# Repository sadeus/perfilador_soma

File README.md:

# Perfilador/Polarimetro SOMA

## Contenido
Se crearon sensores optomecánicos portátiles, para poder medir cambios de los haces de los setups del laboratorio. Todo el marco del proyecto SOMA

### Indice de carpetas
- software: Software para la adquisición y visualización de las mediciones. Acá se efectúa el análisis de los datos obtenidos
- firmware: Código para el uC para el polarimetro/perfilador. Tiene un makefila con los métodos usuales
- circuito: Diseño del circuito impreso
- perfilador: Diseño mecánico del perfilador
- polarimetro: Diseño mecánico del polarimetro
- espectrometro: Diseño del circuito para el espectrómetro (EN PROGRESO)

## Instalación

Para poder instalar y usar el software/firmware de este proyecto es necesario tener [NodeJS](https://nodejs.org/es/):

- Linux, macOS: Instalación por manejador de paquetes, [aquí](https://nodejs.org/es/download/package-manager/)
- Windows: Descargar binario de la página oficial

En una command prompt o terminal escribir lo siguiente para instalar dependencias

```npm install```

Esto instala las dependencias de firmware y software. Para obtener ayuda de los comandos disponibles ejecutar

```npm run```

### Lista de comandos
- `npm run ip`: abre el puerto serie creado al conectar el uC y obtiene la ip del dispositivo
- `npm run start`: inicia el servidor web del software de adquisición. Por defecto se entra en un browser en http://localhost:9000
- `npm run compile`: compila el firmware. Para compilar el firmware, por ahora, es necesario logearse con `npm run login` y una cuenta de [particle.io](http://build.particle.io)
- `npm run upload`: Actualiza el firmware del uC por USB. Es necesario tener el uC en modo DFU (ver [acá](https://docs.particle.io/guide/getting-started/modes/photon/#dfu-mode-device-firmware-upgrade-))

## Dependencias

### Software
- Python v3.5.0
- Numpy v1.11.3
- Pandas v0.19.2
- Matplotlib v2.0.0
- Scipy v0.18.1
- Flask v0.12
- Web browser (Firefox, Chrome, Safari, _no funciona en IE_)

### Firmware
Para compilar, flashear y escuchar el puerto Serie del uC es necesario tener:
- NodeJS v6.0
- Particle-cli v1.21.0
- readline-sync (para interfaz interactiva)

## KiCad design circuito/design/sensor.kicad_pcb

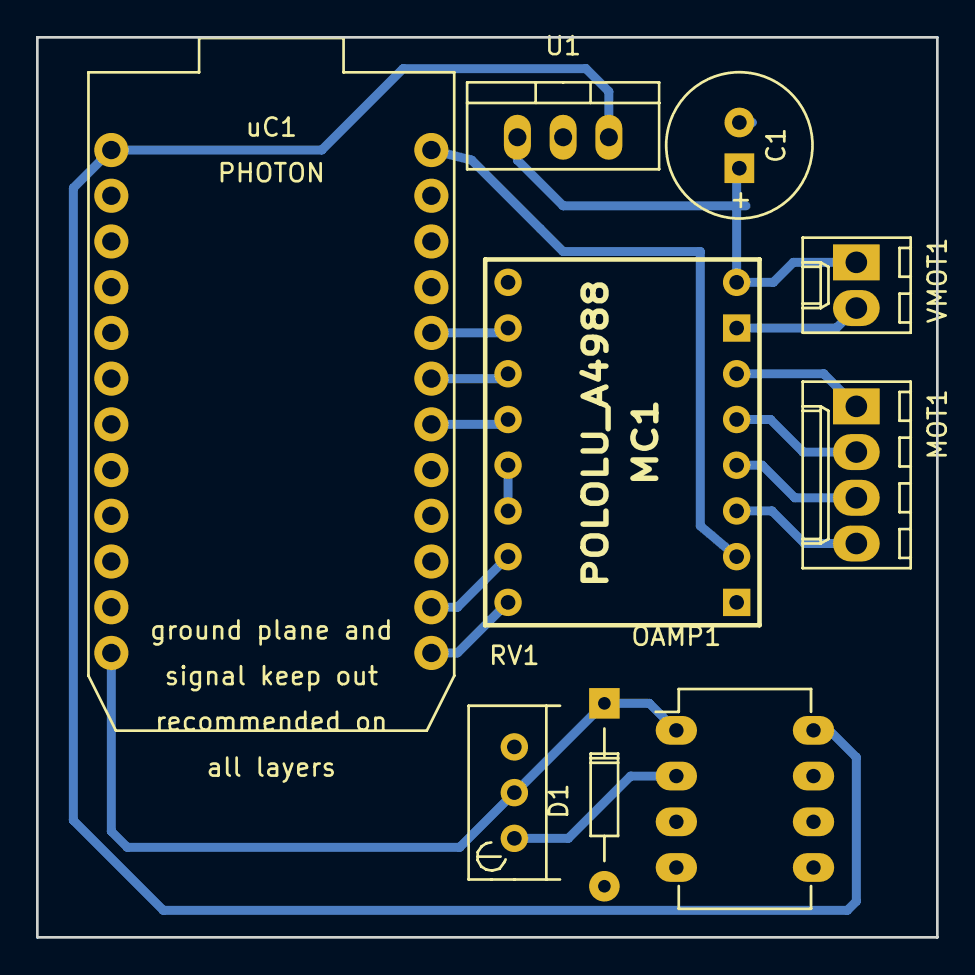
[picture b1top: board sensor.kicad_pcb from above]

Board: 2 copper layers, 50.0 x 50.0 mm, 9 parts (0 on the bottom side), 16 nets.

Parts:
C1: 100uF; C1V8
D1: 3.3V; Diode_DO-35_SOD27_Horizontal_RM10
MC1: POLOLU_A4988; SWDIP8_.6W
MOT1: CONN_01X04; Molex_KK_6410-04
OAMP1: LM358; DIP-8_W7.62mm_LongPads
RV1: 10K; Potentiometer_Bourns_3296W_3-8Zoll_Inline_ScrewUp
U1: 7805; TO-220_Neutral123_Vertical
VMOT1: CONN_01X02; Molex_KK_6410-02
uC1: PHOTON

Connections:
+3V3: MC1.2, uC1.24
+5V: OAMP1.8, U1.3, uC1.1
+12V: C1.1, MC1.8, U1.1, VMOT1.1
/ADC: D1.1, OAMP1.1, RV1.2, uC1.12
/DIR: MC1.16, uC1.13
/MS1: MC1.10, uC1.20
/MS2: MC1.11, uC1.19
/MS3: MC1.12, uC1.18
/STEP: MC1.15, uC1.14
GND: C1.2, D1.2, MC1.1, MC1.7, OAMP1.3, OAMP1.4, U1.2, VMOT1.2, uC1.2
unnamed: MC1.3, MOT1.4
unnamed: MC1.4, MOT1.3
unnamed: MC1.5, MOT1.2
unnamed: MC1.6, MOT1.1
unnamed: MC1.13, MC1.14
unnamed: OAMP1.2, RV1.1

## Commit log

2016-06-13 Se copia desarrollo del GDrive
2016-06-13 Se agrega mediciones, más o menos ordenadas. Se cambia README
2016-06-15 Medición con tambor de plástico
2016-06-15 Nueva iteración, agujero más grande
2016-06-15 Cambios de script menores, nueva medición
2016-06-16 Cambios de gitignore para windows
2016-06-16 Se elimina archivos de thumbnails de windows
2016-06-16 Nueva iteración de soporte
2016-06-16 Carcasa final. Va con un acrilico arriba
2016-06-18 Imagenes para presentación. Nuevos cambios en modelo
2016-06-23 Se ordenaron archivos, se creó nuevo archivo de diseño para polarimetro
2016-06-24 Cambios del engranaje. Agregado mejor interfaz web. Cambio en código de sketch, ahora es compatible con polarimetro
2016-06-30 Nuevo cambio en carcaza
2016-06-30 Se cambio velocidad para polarimetro
2016-06-30 Cambios de diseño.
2016-06-30 Mediciones sin ruido finales. Polarización definida
2016-06-30 Implementación con PyQT en progreso
2016-07-01 Se agrega etiquetas del preprocesador para usar polarimetro y perfilador en la compilación
2016-07-01 Ajustes hechos para datos nuevos
2016-07-01 Commit de charla
2016-07-01 Datos viejos agregados
2016-07-01 Nuevo gitignore
2016-07-01 Medición de spim con plástico PLA
2016-07-01 Mediciones de diferentes laseres, azul y verde
2016-07-01 Cambio de titulo de la charla
2016-07-04 Primer iteración de charla final labo 7
2016-07-05 Segunda iteración y presentación de charla final labo 7
2016-07-12 Nuevos diseños, más archivos dwg/dxf con planos mecánicos
2016-07-12 Cambios en mediciones de perfil
2016-07-15 Cambio final del circuito.
2016-07-15 Reordenado de archivos de informes. Anteúltima iteración del informe final.
2016-07-16 Nueva iteración del informe. Preprint
2016-07-19 Iteración final del informe
2016-09-12 Cambio menor de gui
2016-09-12 Se eliminan archivos binarios
2016-09-12 Cambios menores
2016-09-13 Primer commit de documentación
2016-09-13 Se comprime charla final de laboratorio 7
2016-09-13 Archivos de charla final
2016-09-13 Se comprime archivos de informe de laboratorio 7
2016-09-13 Se agrega documentación
2016-10-05 Primera iteraciÃn del manual
2016-10-11 Circuito funcionando, imprime IP por puerto serie
2016-10-11 Última iteración
2016-10-11 Nueva iteración del manual
2016-10-23 Interfaz funcional, solo crudo
2016-10-23 Sensores funcionando con ip dinámica
2016-11-08 Implementación con 7805
2016-11-08 Web funcionando con uC
2016-12-28 Mejora en interfaz, redescubrimiento de sensor en segmento de red
2016-12-28 Esquemático en formato EAGLE
2017-01-01 Uso de web workers para interfaz web
2017-01-01 Uso de IP en Cloud, a nivel uC
2017-01-01 Cambio de código
2017-01-01 Se organizan views
2017-04-07 Ordenado de archivos
2017-04-07 PDF de ph+motor
2017-04-07 Cambios en makefile, usa node local. Cambios de código
2017-04-07 Cambios en visor web
2017-04-07 Diseño de espectrometro
2017-04-10 Ordenado de adquisición
2017-04-11 Ordenado de web y mejora de esta. Se puede setear la IP
2017-04-11 Reordenado de firmware. Compila y funciona
2017-04-11 Mejora del README con el reordenado. Mas docs
2017-04-11 Firmware corriendo
2017-04-11 Requirements
2017-04-16 Building por npm
2017-04-16 Se pasa a usar assets locales
